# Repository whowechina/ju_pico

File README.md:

# Ju Pico - Jubeat Style Mini Controller
[点这里可以切换到中文版](README_CN.md)

Features:
* There're two versions. Ju Pico is designed for 15.6" portable monitor, Ju Pico+ is designed for 21.5" monitor.
* It's small but closely replicates the feel of the arcade.
* Can be placed in 4 different orientations (rotations).
* Command line for configurations.
* All source files open.

Thanks to many respectful guys/companies who made their tools or materials free or open source (KiCad, OnShape, InkScape, Raspberry things).

Special thanks to community projects and developers.
And also these projects:
* RP_Silicon_KiCad: https://github.com/HeadBoffin/RP_Silicon_KiCad
* Type-C: https://github.com/ai03-2725/Type-C.pretty

## My Other Projects
You can check out my other cool projects.

* Popn Pico: https://github.com/whowechina/popn_pico
* IIDX Pico: https://github.com/whowechina/iidx_pico
* IIDX Teeny: https://github.com/whowechina/iidx_teeny
* Chu Pico: https://github.com/whowechina/chu_pico
* Mai Pico: https://github.com/whowechina/mai_pico
* Diva Pico: https://github.com/whowechina/diva_pico
* AIC Pico: https://github.com/whowechina/aic_pico
* Groove Pico: https://github.com/whowechina/groove_pico
* Geki Pico: https://github.com/whowechina/geki_pico
* Musec Pico: https://github.com/whowechina/musec_pico
* Ju Pico: https://github.com/whowechina/ju_pico

## **Disclaimer** ##
I made this project in my personal time with no financial benefit or sponsorship. I will continue to improve the project. I have done my best to ensure that everything is accurate and functional, there's always a chance that mistakes may occur. I cannot be held responsible for any loss of your time or money that may result from using this open source project. Thank you for your understanding.

## About the License
It's CC-NC. So DIY for yourself and for your friend, don't make money from it. And plagiarism that doesn’t even dare to mention the original author is not acceptable. Please note that pooling orders and group buying for raw materials is acceptable. Selling off any leftover components without profit is also acceptable.

If you're interested in buying from me, or for commercial use, please contact me (Discord, QQ group, Wechat group or leave your contact in issue section).

## My Discord Invitation
https://discord.gg/M8f2PPQFEA

## HOW TO BUILD JU PICO
### PCB and Components
* Go JLCPCB and make order with the gerber zip files (latest `Production\PCB\ju_io_xxx.zip` and `Production\PCB\ju_button_xxx.zip`), regular FR-4 board, black color, **1.6mm** thickness. For Ju Pico+, please use `button215` version.
* 1x Raspberry Pico Pi Pico or pin-to-pin compatible clones (U1).  
  https://www.raspberrypi.com/products/raspberry-pi-pico
* 1x USB Type-C socket (918-418K2023S40001 or KH-TYPE-C-16P)
* 4x WS2812B-3528 RGB LEDs.
* 4x Alps SKPMAPE010 6.0×5.9mm tactile switch in black, Panasonic EVQP1K05M works too, but it only comes in a white version.  
  https://tech.alpsalpine.com/e/products/detail/SKPMAPE010/
* 1x 0603 0.1uF (0.1~1uF all fine) capacitor (C1).
* 2x 0603 5.1kohm resistors (R1, R2) for the USB.
* 8x JST-SH1.0 5-pin SMD connectors (J1 to J4 on IO PCB, and 4 others on button PCBs).
* 1x JST-SH1.0 3-pin SMD connector (J5), optional for future HID light expansion.
* 4x JST-SH1.0 dual-end 5-pin cables (pin 1 to pin 1 mapping): 2 cables of 20cm length, and 2 cables of 30cm length.
* 64x Silicone rubber buttons, **6mm\*7mm**, **4mm** height, with 2 legs. Buy soft (lower actuation force) ones if possible. It looks like this:  
  
* This is how the I/O board looks after soldering.  

* Becareful of 2 pin holes. It's a common oversight to either forget to solder them or to leave air bubbles during the process. To avoid this, solder slowly from one side of the hole, using minimal solder wire and a generous amount of flux.  

### Test the IO PCB
* You can test the PCB now, put the firmware in IO PCB.
* All 4 RGB LEDs should light up in a rainbow pattern.
* LEDs responds to the the leftmost button, indicating current orientation.
* Ju Pico should be recognized as a USB HID device, here's the test page.  
  https://greggman.github.io/html5-gamepad-test/
* Connect the 4 button PCBs to the IO PCB, and use one rubber button to test the button contacts on the PCB, you'll see the status change in said HID test page.

### Button Cap
Ju Pico has 16 buttons, so you need to order 16 button caps.

They are made of clear acrylic, measuring 40mm x 40mm with a corner radius of 1-1.5mm and a thickness of 5mm. All these parameters are IMPORTANT and should be followed closely. A polished bevel of **1.5-2mm** on top edges gives a better feel.

Here's what it looks like.  

### 3D Printing
#### Printing parameters
* PLA (recommended) or PETG.
* Layer height: 0.2mm.
* Walls: 5.
* Infill: >=80%.
* Support: Yes, better with special support material.
* Glue on bed: Yes, it prevents corner warping.
* Files are always in millimeter unit, not inch.

#### Parts
* Note: if you want to build Ju Pico+, please use the files with "+" in the filename.
* You have 3 options for the Frame part, heatset insert version is recommended.
  * Screws are threaded into heatset inserts: `Production\3DPrint\ju_pico_frame_inserts.stl`, black. Please install the heat-set inserts first.
  * Screws are directly threaded into the printed material: `Production\3DPrint\ju_pico_frame.stl`, black. Assembly is easier but the screws may wear out the material over time.
  * Screws are threaded into the hex nuts: `Production\3DPrint\ju_pico_frame_hexnut.stl`, black. Assembly is a bit more complicated but the screws won't wear out the material.
* Panel: `Production\3DPrint\ju_pico_panel.stl`, black, print up-side-down with support (use special support material if possible).
* Banner: `Production\3DPrint\ju_pico_banner.3mf`, multi-color, print up-side-down, mainbody is black, LED windows are transparent, logos are red or orange, use special support material if possible.
* 16x Button Seats: `Production\3DPrint\ju_pico_button_seat_*.stl`, black, print up-side-down to avoid overhanging. Choose the one that fits your button cap.
* All together, they look like these.  
  
* Note: Files with "bambu" in the name are project files prepared for Bambu Studio.
* CAUTION: Do not mix use files before and after December 2024, as I made some incompatible changes in early December 2024.

### CNC Aluminum Processing (Optional, only available for Ju Pico)
* If you're into that sleek metal look and don't mind splurging a bit, you can get the frame, panel, and banner parts CNC machined from aluminum.
* Sandblasting and anodizing can be chosen to make it look even better.
* The STEP files are in `Production\CNC` folder, the 2D DWG file is the thread tapping drawing for the frame part.
* You need to 3D print `Production\3DPrint\ju_pico_led_diffuser_for_cnc.stl` for LED diffusion, use transparent material.

### Assembly
#### Other Materials Needed
1. Clear soft/flexible glue or UV curing glue. WARNING: Avoid using any cyanoacrylate-based glue, such as 502. Any glue with a similar smell should also be avoided, as they will leave white smoke marks on the acrylic.
2. 40x **M2\*6mm** (for regular frame) or **M2\*7mm** (for hex nut frame or heatset insert frame) screws, black, for the panel.
3. 4x **M3\*8mm** screws, black, for the banner.
4. 40x **M2** hex nuts (only for hex nut frame version).
5. 40x **M2\*3mm\*3mm** heat-set inserts (only for heatset insert frame version).

### Step by Step
1. Glue the button bodies to the button seats. Be careful don't let the glue ruin the acrylic. See the "Caution" section below for more details.  
   
2. Insert the silicone rubber buttons into the button PCBs. Ensure to pull the legs so that the button sits perfectly flush against the PCB.  
   
3. Use a sharp side cutter to trim the legs of the rubber buttons so that they are flush with the PCB, leaving no protruding parts.  
    
4. Put button PCBs into the frame part and use the cables to connect them to the IO PCB.  
   
5. Arrange the cables and make them fit in the cable slots.  
   
6. If you arrange them well, it will look very neat.  
   
7. Gently put the finished buttons onto the button PCBs.  
   
8. Attach the panel part and secure it with (a lot) M2 screws. Be very careful, 3D print materials are fragile and sensitive to heat. So screw slowly, especially when using a power screwdriver, as the threads in the plastic can easily strip. Lastly put on the banner part and use M3 screws to fix it. And there you go!  

#### Caution
Each 3D printer and filament has its own tolerance, as does the acrylic cutting service. Therefore, I've created multiple versions of the button seat. You can try them and select the one that fits your acrylic button cap perfectly.

## Firmware
* UF2 file is in `Production\Firmware` folder.
* For the new build, hold the BOOTSEL button while connect the USB to a PC, there will be a disk named "RPI-RP2" showed up. Drag the UF2 firmware binary file into it. That's it. There's a small hole at the bottom side of the Ju Pico, it is facing right to the BOOTSEL button.
* If it's already running Ju Pico firmware, you can either use "update" in command line or hold down at least 4 buttons while connecting to USB to enter update mode.
* To access the command line, you can use this Web Serial Terminal to connect to the USB serial port of the Ju Pico. (Note: "?" is for help)  
  https://googlechromelabs.github.io/serial-terminal/

### Usage
* Attach the Ju Pico to a 15.6-inch portable monitor (or Ju Pico+ to a 21.5-inch monitor) using VHB residue-free adhesive tape. Use 3 to 4 small pieces on the monitor's frame, but avoid placing any on the screen. Position it in the orientation that best suits your needs.
* Press the auxiliary button closest to letter 'j" of the logo "Ju Pico" together with the top left main button in the actual placement to set button order that matches your orientation. Analog joystick position in HID report indicates which side the logo should be. You can use the following website to see the joystick status.  
  https://greggman.github.io/html5-gamepad-test/

## CAD Source File
I'm using OnShape free subscription. It's powerful but it can't archive original designs to local, so I can only share the link here. STL/DXF/DWG files are exported from this online document.  
  https://cad.onshape.com/documents/c70fd7c4cb933fd28c4678b3/w/277dab41d8d592c817e9419a/e/e9cf38ee55134a09b2deb5d6

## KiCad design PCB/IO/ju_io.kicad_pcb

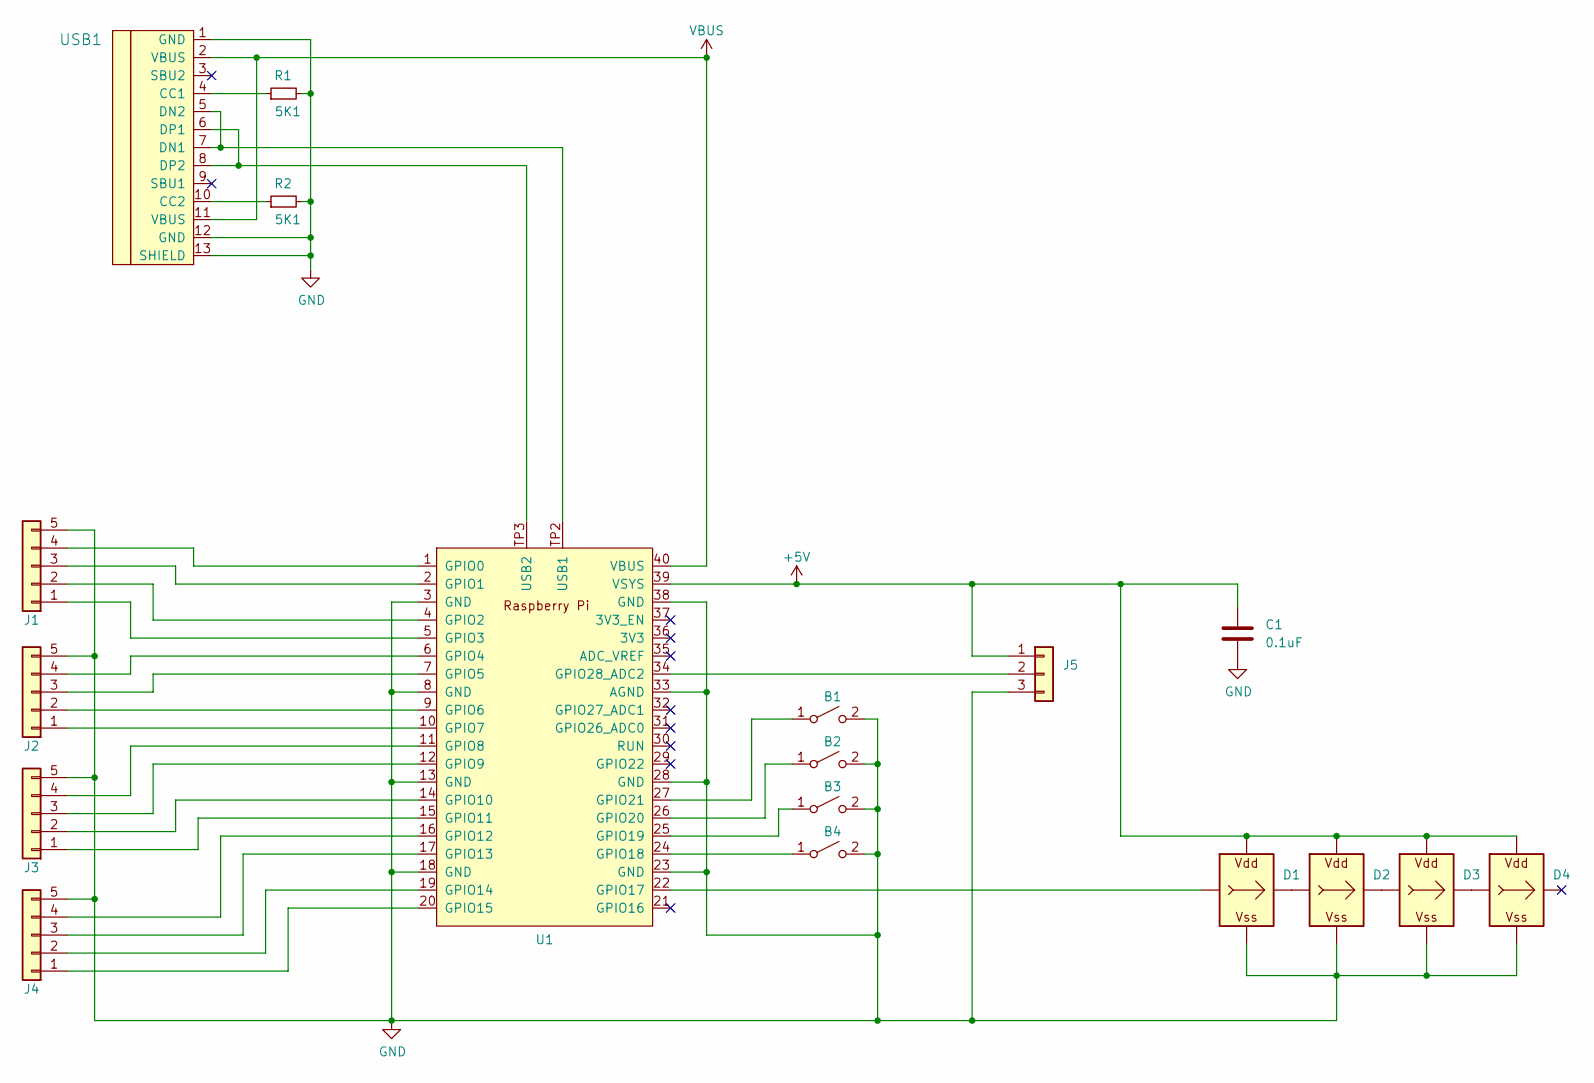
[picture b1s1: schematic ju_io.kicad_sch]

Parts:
B1, B2, B3, B4: SW_SPST; EVQP1K05M
C1: 0.1uF; C_0603_1608Metric_Pad1.08x0.95mm_HandSolder
D1, D2, D3, D4: WS2812B_Unified; WS2812B-2835
J1, J2, J3, J4: Conn_01x05; SH1.0_5P
J5: Conn_01x03; SH1.0_3P
R1, R2: 5K1; R_0603_1608Metric_Pad0.98x0.95mm_HandSolder; LCSC C23186
U1: PiPico_No_SWD; RPi_Pico_SMD_Pins_No_SWD_No_Text
USB1: U262-161N-4BVC11; HRO-TYPE-C-31-M-12-Assembly; LCSC C319148

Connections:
+5V: C1.1, D1.V (VDD), D2.V (VDD), D3.V (VDD), D4.V (VDD), J5.1, U1.39 (VSYS)
GND: B1.2 (B), B2.2 (B), B3.2 (B), B4.2 (B), C1.2, D1.G (VSS), D2.G (VSS), D3.G (VSS), D4.G (VSS), J1.5, J2.5, J3.5, J4.5, J5.3, R1.2, R2.2, U1.3 (GND), U1.8 (GND), U1.13 (GND), U1.18 (GND), U1.23 (GND), U1.28 (GND), U1.33 (AGND), U1.38 (GND), USB1.1 (GND), USB1.12 (GND), USB1.13 (SHIELD)
unnamed: B1.1 (A), U1.27 (GPIO21)
unnamed: B2.1 (A), U1.26 (GPIO20)
unnamed: B3.1 (A), U1.25 (GPIO19)
unnamed: B4.1 (A), U1.24 (GPIO18)
unnamed: D1.I (In), U1.22 (GPIO17)
unnamed: D1.O (Out), D2.I (In)
unnamed: D2.O (Out), D3.I (In)
unnamed: D3.O (Out), D4.I (In)
unnamed: J1.1, U1.5 (GPIO3)
unnamed: J1.2, U1.4 (GPIO2)
unnamed: J1.3, U1.2 (GPIO1)
unnamed: J1.4, U1.1 (GPIO0)
unnamed: J2.1, U1.10 (GPIO7)
unnamed: J2.2, U1.9 (GPIO6)
unnamed: J2.3, U1.7 (GPIO5)
unnamed: J2.4, U1.6 (GPIO4)
unnamed: J3.1, U1.15 (GPIO11)
unnamed: J3.2, U1.14 (GPIO10)
unnamed: J3.3, U1.12 (GPIO9)
unnamed: J3.4, U1.11 (GPIO8)
unnamed: J4.1, U1.20 (GPIO15)
unnamed: J4.2, U1.19 (GPIO14)
unnamed: J4.3, U1.17 (GPIO13)
unnamed: J4.4, U1.16 (GPIO12)
unnamed: J5.2, U1.34 (GPIO28_ADC2)
unnamed: U1.TP2 (USB1), USB1.5 (DN2), USB1.7 (DN1)
unnamed: U1.TP3 (USB2), USB1.6 (DP1), USB1.8 (DP2)
unnamed: R1.1, USB1.4 (CC1)
unnamed: R2.1, USB1.10 (CC2)
VBUS: U1.40 (VBUS), USB1.2 (VBUS), USB1.11 (VBUS)

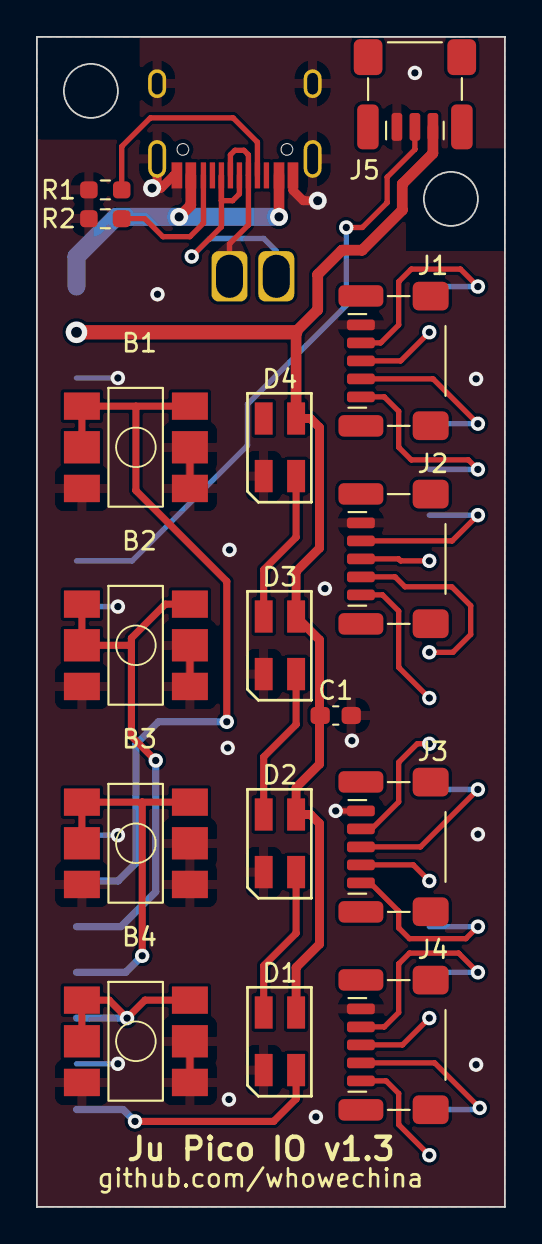
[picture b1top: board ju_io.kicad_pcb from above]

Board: 2 copper layers, 26.0 x 65.0 mm, 18 parts (1 on the bottom side), 32 nets.

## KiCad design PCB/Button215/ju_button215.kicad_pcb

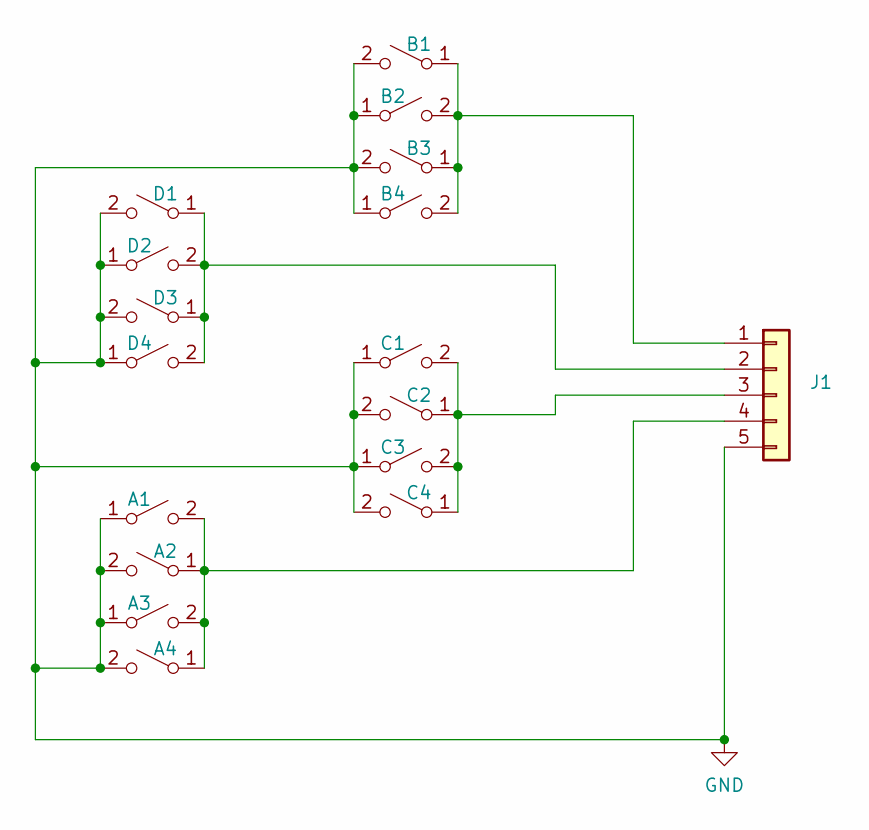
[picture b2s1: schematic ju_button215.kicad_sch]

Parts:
A1, A2, A3, A4: SW_SPST; JuRubber
B1, B2, B3, B4: SW_SPST; JuRubber
C1, C2, C3, C4: SW_SPST; JuRubber
D1, D2, D3, D4: SW_SPST; JuRubber
J1: Conn_01x05; SH1.0_5P

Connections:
GND: A1.1 (A), A2.2 (B), A3.1 (A), A4.2 (B), B1.2 (B), B2.1 (A), B3.2 (B), B4.1 (A), C1.1 (A), C2.2 (B), C3.1 (A), C4.2 (B), D1.2 (B), D2.1 (A), D3.2 (B), D4.1 (A), J1.5
unnamed: A1.2 (B), A2.1 (A), A3.2 (B), A4.1 (A), J1.4
unnamed: B1.1 (A), B2.2 (B), B3.1 (A), B4.2 (B), J1.1
unnamed: C1.2 (B), C2.1 (A), C3.2 (B), C4.1 (A), J1.3
unnamed: D1.1 (A), D2.2 (B), D3.1 (A), D4.2 (B), J1.2

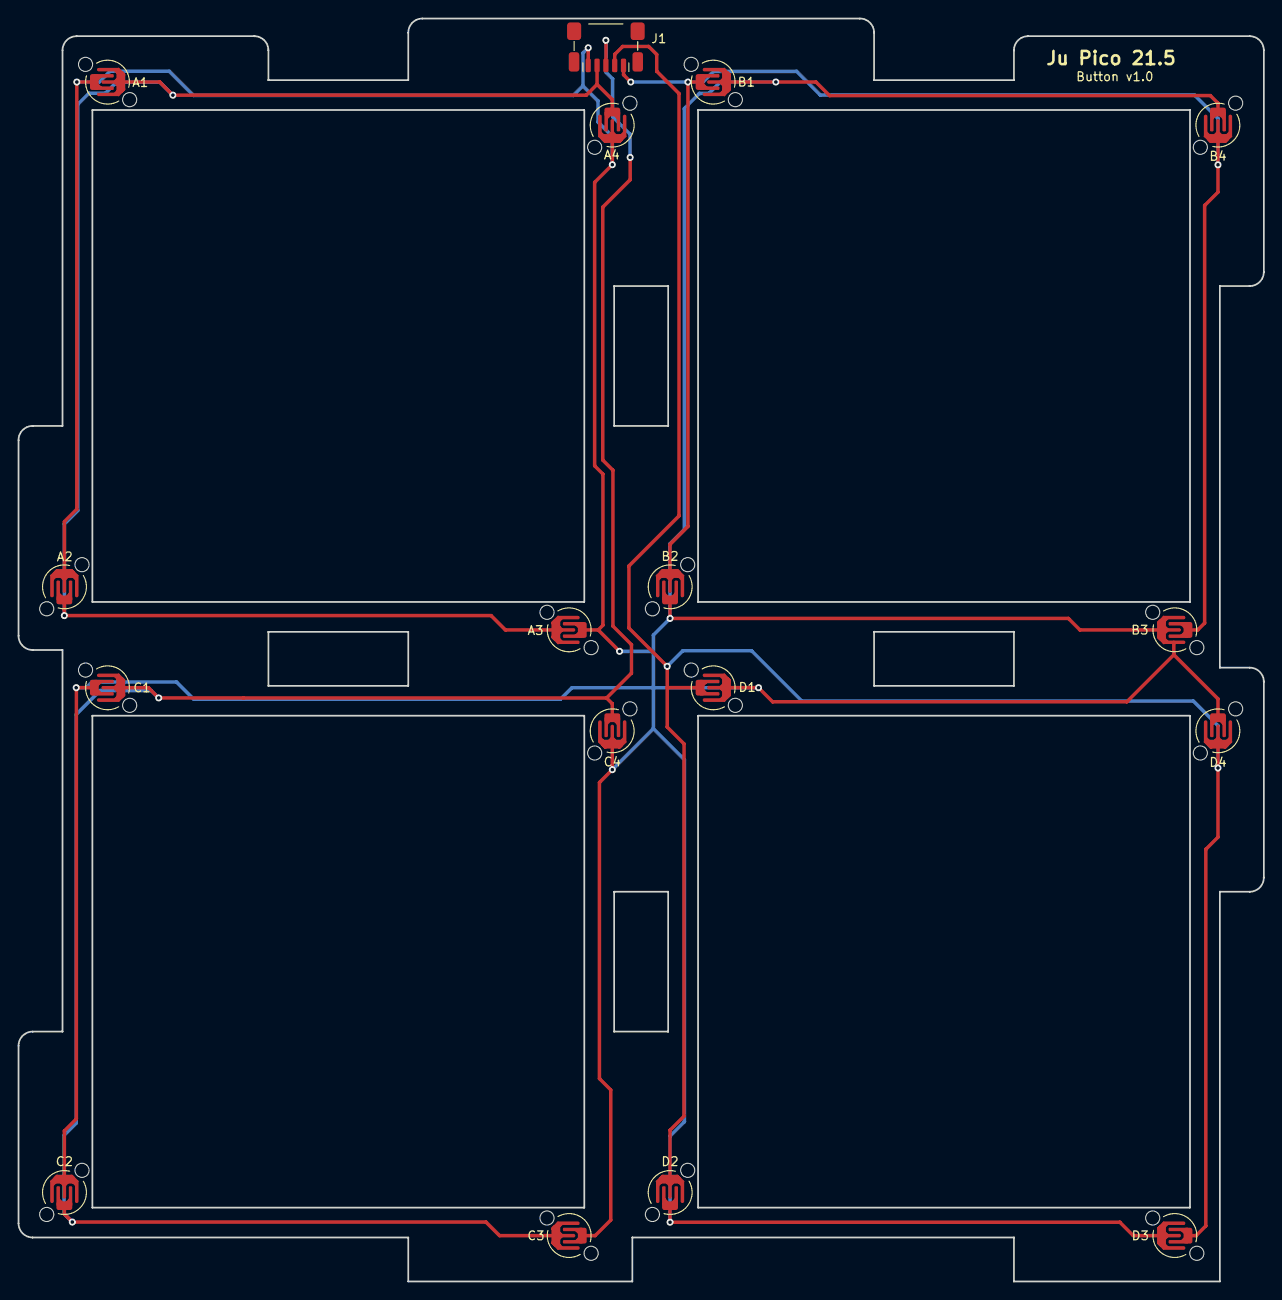
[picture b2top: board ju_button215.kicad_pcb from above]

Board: 2 copper layers, 141.1 x 143.1 mm, 17 parts (0 on the bottom side), 5 nets.

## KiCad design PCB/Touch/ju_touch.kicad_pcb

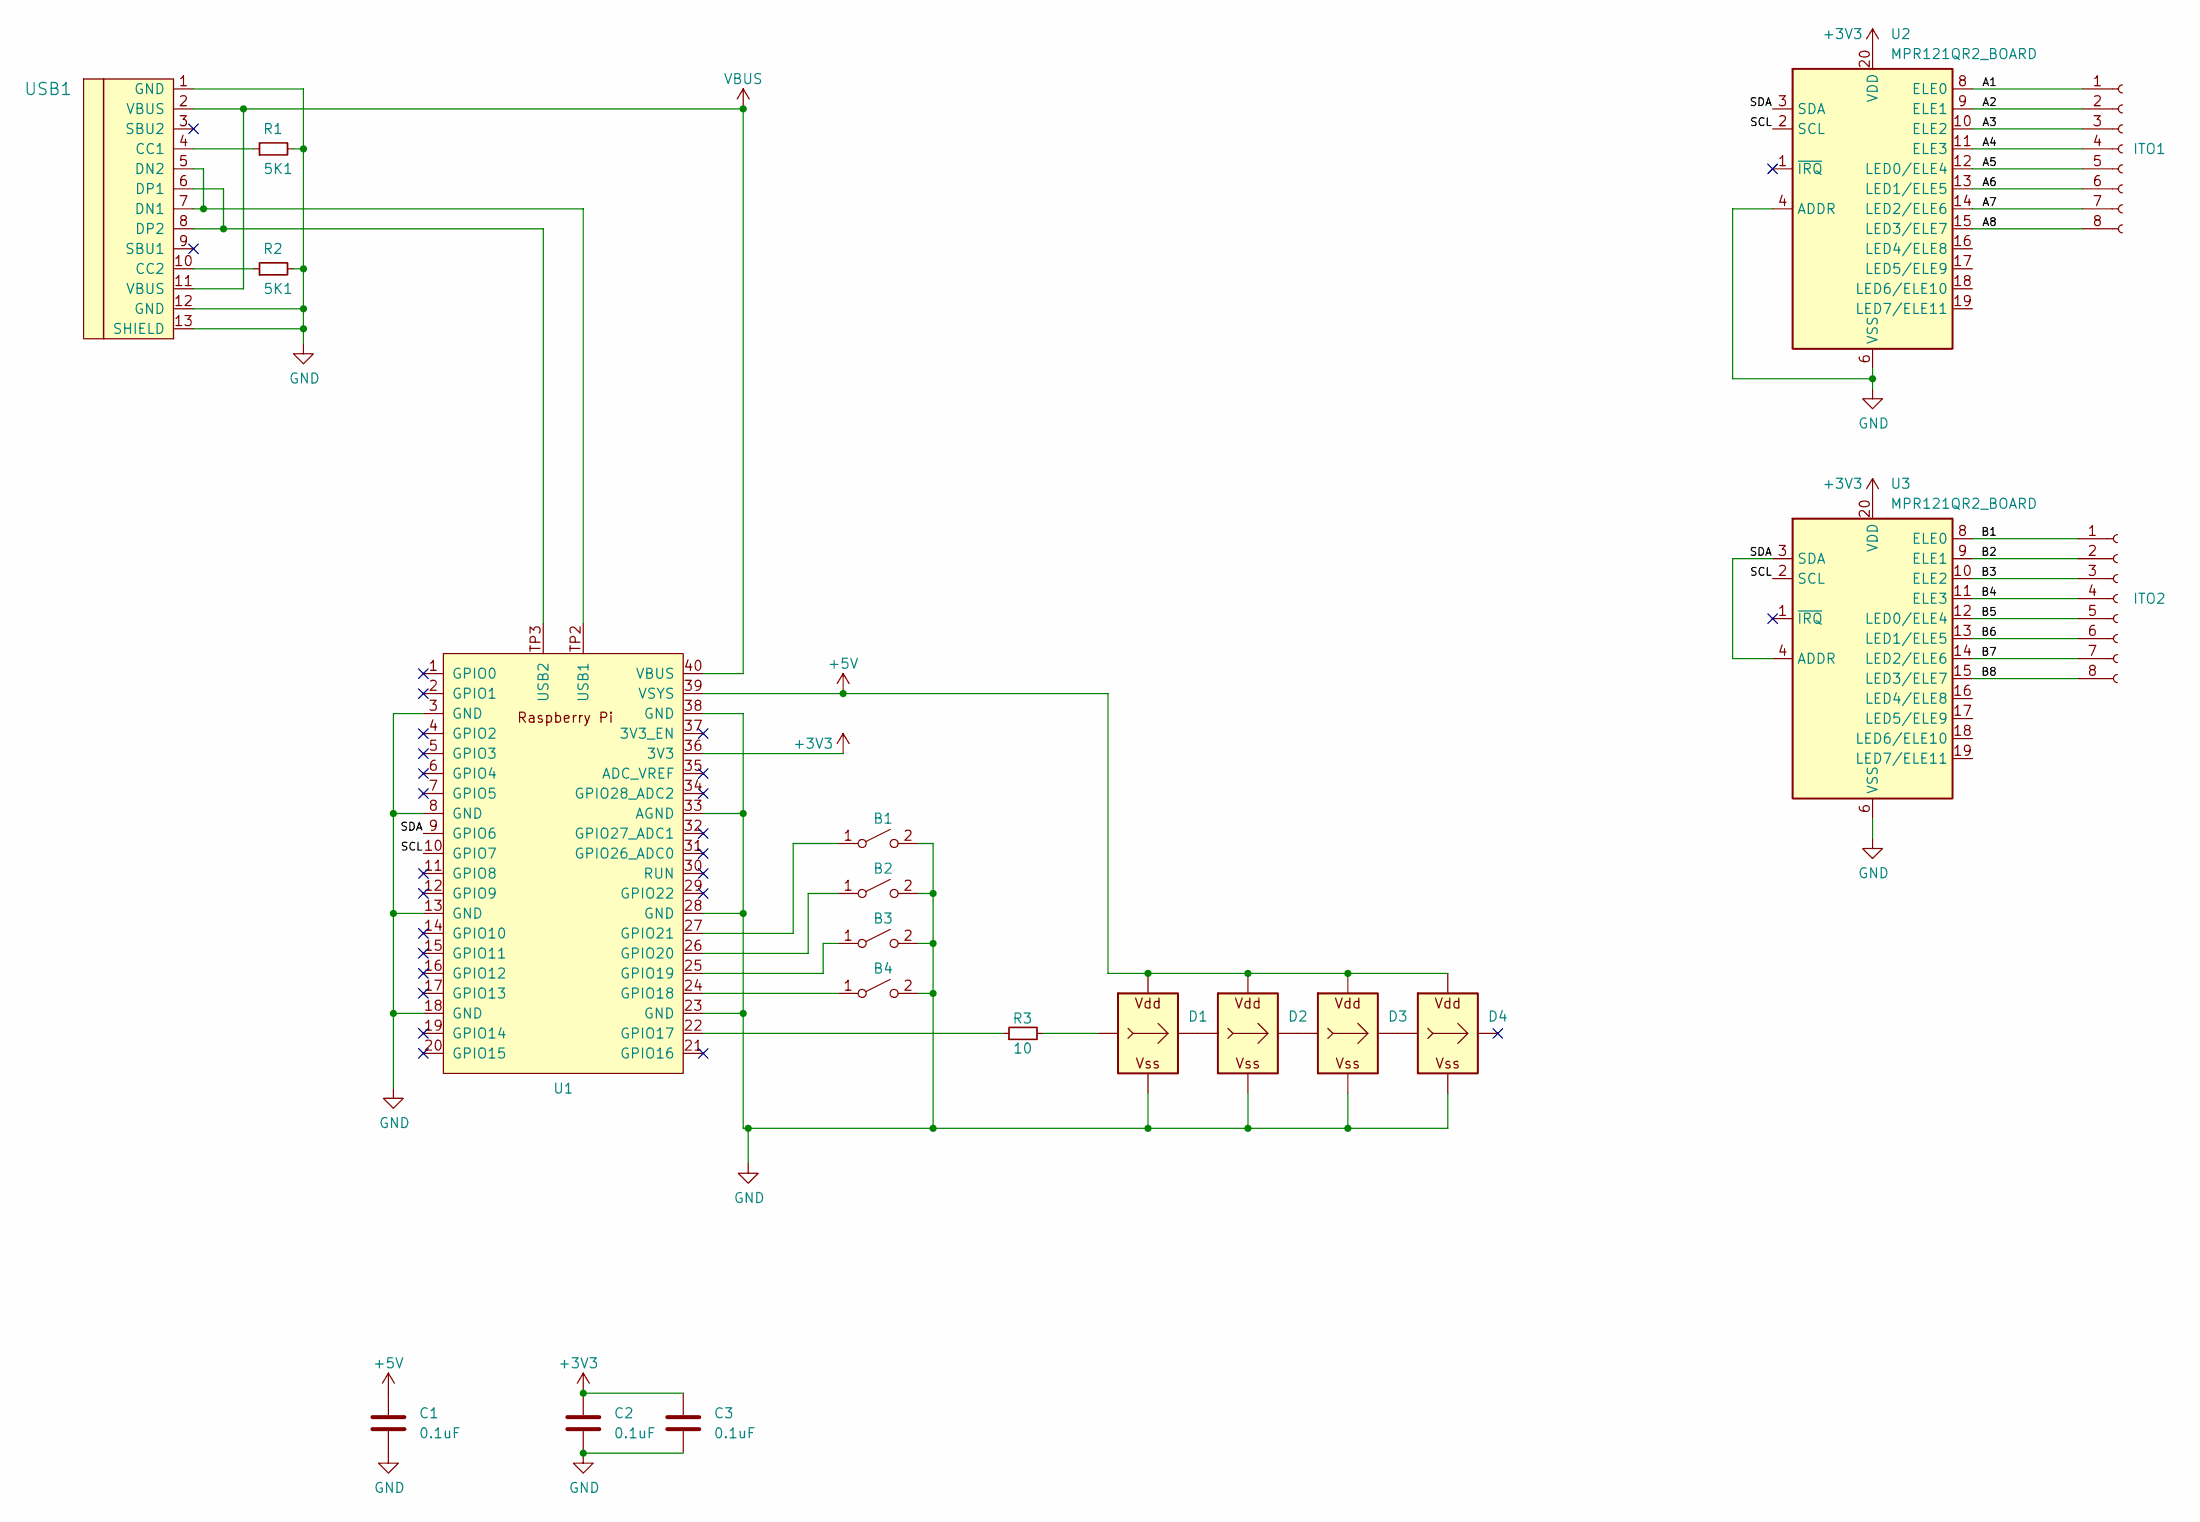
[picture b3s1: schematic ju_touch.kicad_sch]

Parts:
B1, B2, B3, B4: SW_SPST; EVQP1K05M
C1, C2, C3: 0.1uF; C_0603_1608Metric_Pad1.08x0.95mm_HandSolder
D1, D2, D3, D4: WS2812B_Unified; WS2812B-2835
ITO1, ITO2: Conn_01x08_Socket; JuTouch_Conn8
R1, R2: 5K1; R_0603_1608Metric_Pad0.98x0.95mm_HandSolder; LCSC C23186
R3: 10; R_0603_1608Metric_Pad0.98x0.95mm_HandSolder; LCSC C23186
U1: PiPico_No_SWD; RPi_Pico_SMD_Pins_No_SWD_No_Text
U2, U3: MPR121QR2_BOARD; MPR121_BOARD
USB1: U262-161N-4BVC11; HRO-TYPE-C-31-M-12-Assembly; LCSC C319148

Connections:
+3V3: C2.1, C3.1, U1.36 (3V3), U2.20 (VDD), U3.20 (VDD)
+5V: C1.1, D1.V (VDD), D2.V (VDD), D3.V (VDD), D4.V (VDD), U1.39 (VSYS)
/A1: ITO1.1, U2.8 (ELE0)
/A2: ITO1.2, U2.9 (ELE1)
/A3: ITO1.3, U2.10 (ELE2)
/A4: ITO1.4, U2.11 (ELE3)
/A5: ITO1.5, U2.12 (LED0/ELE4)
/A6: ITO1.6, U2.13 (LED1/ELE5)
/A7: ITO1.7, U2.14 (LED2/ELE6)
/A8: ITO1.8, U2.15 (LED3/ELE7)
/B1: ITO2.1, U3.8 (ELE0)
/B2: ITO2.2, U3.9 (ELE1)
/B3: ITO2.3, U3.10 (ELE2)
/B4: ITO2.4, U3.11 (ELE3)
/B5: ITO2.5, U3.12 (LED0/ELE4)
/B6: ITO2.6, U3.13 (LED1/ELE5)
/B7: ITO2.7, U3.14 (LED2/ELE6)
/B8: ITO2.8, U3.15 (LED3/ELE7)
/SCL: U1.10 (GPIO7), U2.2 (SCL), U3.2 (SCL)
/SDA: U1.9 (GPIO6), U2.3 (SDA), U3.3 (SDA), U3.4 (ADDR)
GND: B1.2 (B), B2.2 (B), B3.2 (B), B4.2 (B), C1.2, C2.2, C3.2, D1.G (VSS), D2.G (VSS), D3.G (VSS), D4.G (VSS), R1.2, R2.2, U1.3 (GND), U1.8 (GND), U1.13 (GND), U1.18 (GND), U1.23 (GND), U1.28 (GND), U1.33 (AGND), U1.38 (GND), U2.4 (ADDR), U2.6 (VSS), U3.6 (VSS), USB1.1 (GND), USB1.12 (GND), USB1.13 (SHIELD)
unnamed: B1.1 (A), U1.27 (GPIO21)
unnamed: B2.1 (A), U1.26 (GPIO20)
unnamed: B3.1 (A), U1.25 (GPIO19)
unnamed: B4.1 (A), U1.24 (GPIO18)
unnamed: D1.I (In), R3.2
unnamed: D1.O (Out), D2.I (In)
unnamed: D2.O (Out), D3.I (In)
unnamed: D3.O (Out), D4.I (In)
unnamed: R3.1, U1.22 (GPIO17)
unnamed: U1.TP2 (USB1), USB1.5 (DN2), USB1.7 (DN1)
unnamed: U1.TP3 (USB2), USB1.6 (DP1), USB1.8 (DP2)
unnamed: R1.1, USB1.4 (CC1)
unnamed: R2.1, USB1.10 (CC2)
VBUS: U1.40 (VBUS), USB1.2 (VBUS), USB1.11 (VBUS)

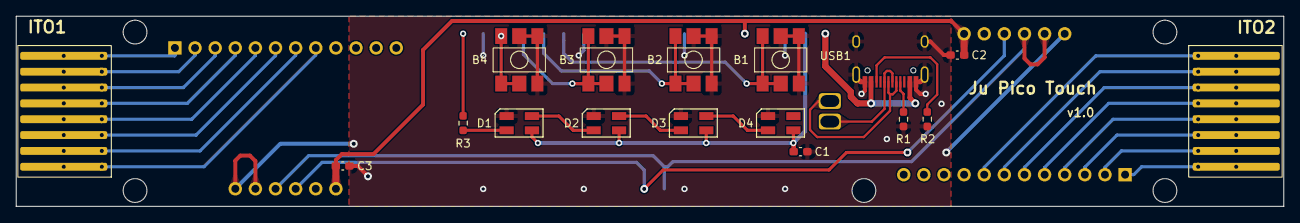
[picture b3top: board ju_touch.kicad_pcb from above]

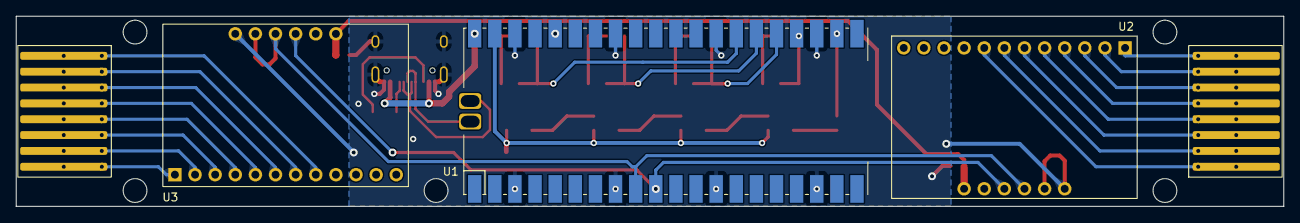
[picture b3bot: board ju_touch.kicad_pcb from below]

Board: 2 copper layers, 160.0 x 24.0 mm, 20 parts (5 on the bottom side), 35 nets.

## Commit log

2024-10-23 Initial commit (PCB v1.0)
2024-10-27 Firmware
2024-10-27 PCBs of v1.1
2024-11-02 Rotate, update check and HID compatibility
2024-11-02 PCB optimization button v1.2, io v1.21
2024-11-06 Ju Touch PCB into Ju Pico repo
2024-11-06 Button PCB v1.2 files (missing from previous commit)
2024-11-08 Runtime rotate control
2024-11-09 Finished guide for Ju Pico (Ju Touch not there yet)
2024-11-10 Minor fix in guide
2024-11-10 Bambu project for banner print
2024-11-11 Screw hole and cable slot small improvement
2024-11-11 More seat tolerance options
2024-11-11 Connector marks in guide
2024-11-13 Screw cautions
2024-11-14 Analog axis reports rotate mode
2024-11-23 Cross-reference
2024-12-04 CNC and Hex nuts option
2024-12-04 Remove Ju Touch
2024-12-06 LED Diffuser for CNC
2025-01-04 Fix getchar return handling
2025-01-04 Better polling rate
2025-02-12 Screw option description for the hex nut frame
2025-03-29 Frame with heat set insert option
2025-04-28 Fix 40.0 and 40.2 button seats
2025-05-12 Ju Pico IO PCB v1.22
2025-06-16 PCB folder cleanup
2025-06-24 Change the way of button mapping
2025-07-06 Ju Matrix firmware startts
2025-07-07 LED panel working with FPS counting
2025-07-08 More types of markers in Ju Matrix
2025-07-08 PCB for 21.5
2025-07-08 Geber for 21.5 button PCB
2025-07-10 Markers supported
2025-07-11 Markers 8bit + 8bit and fontsnat 4bit
2025-07-11 dma fill for performance
2025-07-14 Button statistics
2025-07-14 Better debouncing
2025-08-01 Fix io conflict between save and matrix
2025-08-01 matrix->grid->marker abstraction
2025-08-02 JubeatHax interfacing roughly working
2025-08-03 Preview and result screen
2025-08-03 Sanitize font name in font tool
2025-08-04 Ju Pico better report timing
2025-08-04 Add Ju Matrix Plus
2025-08-06 Result page done (dumped old fontgen)
2025-08-06 Better defaults
2025-08-06 Fix phase change
2025-08-06 Ju Matrix Plus crop mode
2025-08-06 Playable, but no long notes yet
2025-08-07 Simple trail implementation
2025-08-08 Image plotter separate from marker
2025-08-08 Trail resource added
2025-08-08 Fix image alpha bug
2025-08-08 Better font for result
2025-08-09 Smooth font movement
2025-08-09 Put trail into cell structure
2025-08-10 Long note (trail) kinda works
2025-08-10 Fix long trail marker
2025-08-10 Trail resources
2025-08-14 Local trail timing sync with remote
2025-08-14 Skip growing animation on short time trails
2025-08-24 Explaining DEBUG mode
2025-08-24 grid_punch for future timing sync
2025-08-25 Monotype font resource
2025-10-21 Ju IO PCB v1.3 (just text change)
2025-11-22 HID Rotate report can be turned off
2025-12-29 Upload missing io PCB
2026-01-03 Ju Pico+ 3D files
2026-01-30 Ju Pico+ in README
2026-02-02 Add missing pico+ panel
2026-03-20 Enlarge some screw holes
2026-04-29 Correct last UF2 location
